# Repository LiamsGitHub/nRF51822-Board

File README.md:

nRF51822-Board
==============

Demo board for Bluetooth Low Energy nRF51822 from Nordic Micro. Eagle CAD tools.

The .brd and .sch files were created with Eagle v6.5.0 for Mac OS

This design is provided solely for the purposes of experimentation.
It is not warranted to work or to comply to any govenment regulation whatsoever.
User is free to download, use and modify and does so entirely at their own risk.

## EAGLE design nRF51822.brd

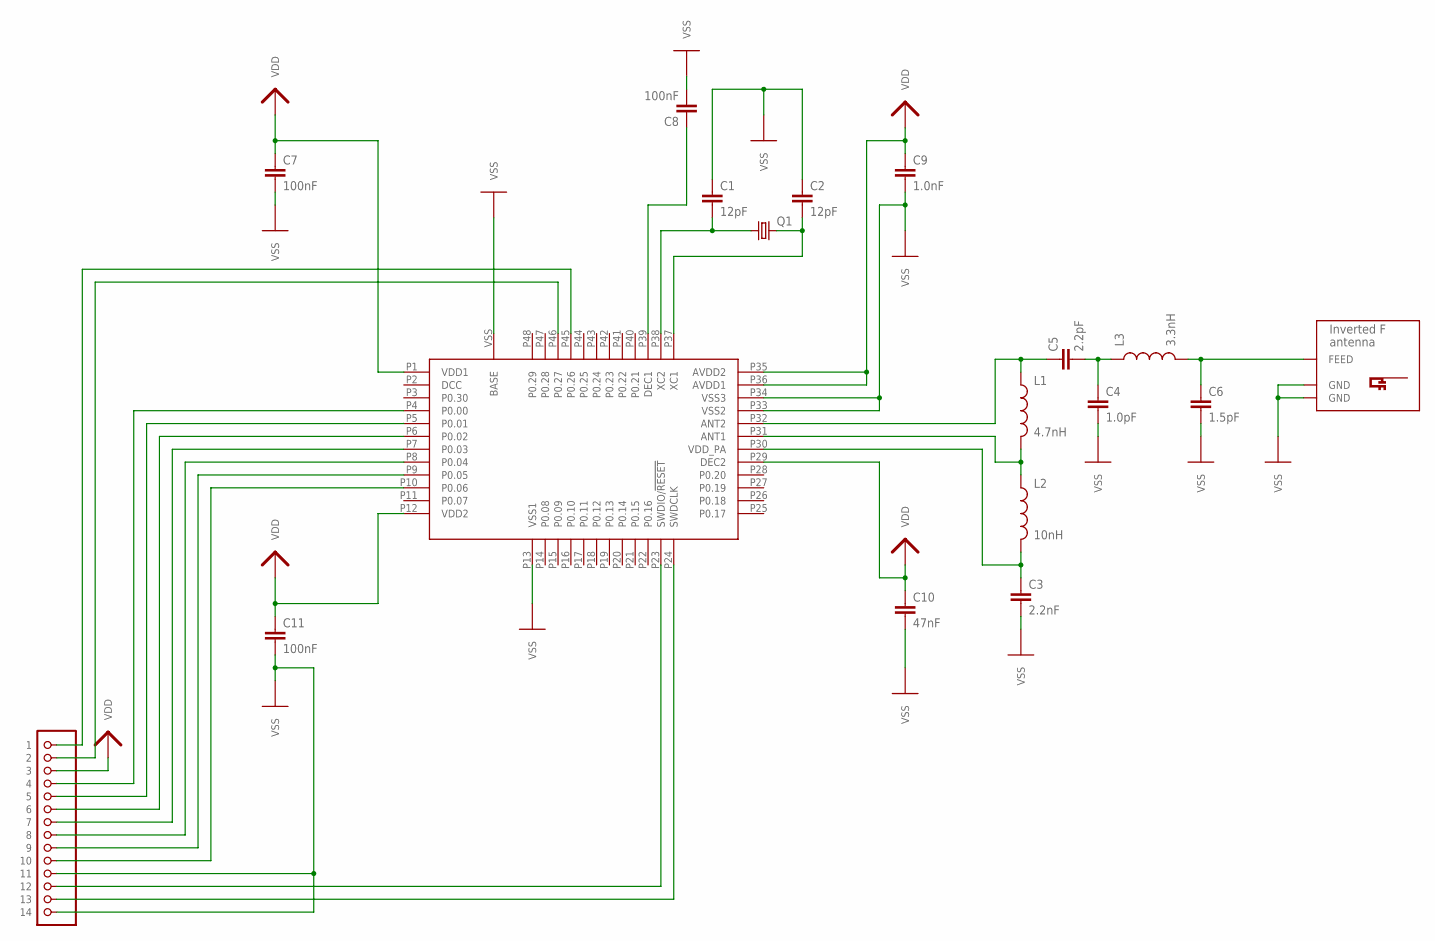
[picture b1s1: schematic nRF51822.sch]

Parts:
C1, C2: 12pF; 0805
C3: 2.2nF; 0805
C4: 1.0pF; 0805
C5: 2.2pF; 0805
C6: 1.5pF; 0805
C7, C8, C11: 100nF; 0805
C9: 1.0nF; 0805
C10: 47nF; 0805
L1: 4.7nH; 0805
L2: 10nH; 0805
L3: 3.3nH; 0805
Q1: FC-12M
U1: nRF51822; QFN48
U$2: INVERTED_F_ANTENNA+2; DN007+2
U$3: PINHD-1X14; 1X14

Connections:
unnamed: C1.2, Q1.1, U1.P38 (XC2)
unnamed: C2.2, Q1.2, U1.P37 (XC1)
unnamed: C3.1, L2.2, U1.P30 (VDD_PA)
unnamed: U1.P45 (P0.26), U$3.1
unnamed: C8.1, U1.P39 (DEC1)
unnamed: C5.1, L1.1, U1.P32 (ANT2)
unnamed: C4.1, C5.2, L3.1
unnamed: C6.1, L3.2, U$2.FEED
unnamed: U1.P46 (P0.27), U$3.2
unnamed: U1.P4 (P0.00), U$3.4
unnamed: U1.P5 (P0.01), U$3.5
unnamed: L1.2, L2.1, U1.P31 (ANT1)
unnamed: U1.P6 (P0.02), U$3.6
unnamed: U1.P7 (P0.03), U$3.7
unnamed: U1.P8 (P0.04), U$3.8
unnamed: U1.P9 (P0.05), U$3.9
unnamed: U1.P10 (P0.06), U$3.10
unnamed: U1.P23 (SWDIO/!RESET!), U$3.12
unnamed: U1.P24 (SWDCLK), U$3.13
VDD: C7.1, C9.1, C10.1, C11.1, U1.P1 (VDD1), U1.P12 (VDD2), U1.P29 (DEC2), U1.P35 (AVDD2), U1.P36 (AVDD1), U$3.3
VSS: C1.1, C2.1, C3.2, C4.2, C6.2, C7.2, C8.2, C9.2, C10.2, C11.2, U1.P13 (VSS1), U1.P33 (VSS2), U1.P34 (VSS3), U1.VSS (BASE), U$2.GND, U$2.GND@1 (GND), U$3.11, U$3.14

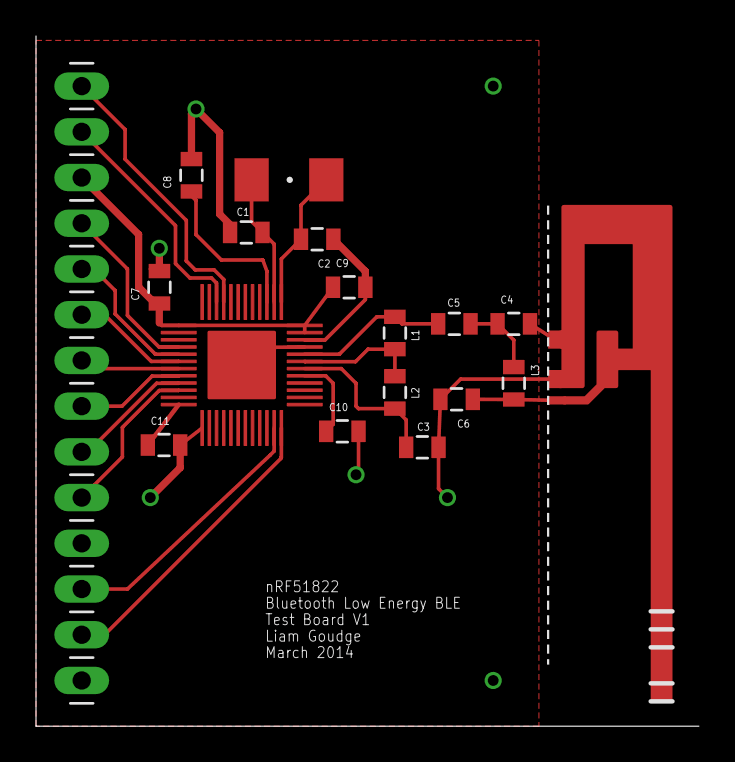
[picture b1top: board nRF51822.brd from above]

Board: 2 copper layers, 36.8 x 38.3 mm, 18 parts (0 on the bottom side), 21 nets.

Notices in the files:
parts and their libraries:
SparkFun-Capacitors: Licensing: CC v3.0 Share-Alike You are welcome to use this library for commercial purposes.
